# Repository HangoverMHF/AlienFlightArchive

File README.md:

## NOTE: This is an archival copy of the original CC BY-SA AlienFlight flight controllers. Preserved for posterity.

# AlienFlight

| [Classic FC](/Flight-Controllers/Classic#narrow-classic-flight-controller) | [F3 Quad FC](/Flight-Controllers/F3-V1/F3-Quad#f3-quad-brushed-v1-flight-controller) | [F3 Hexa FC](/Flight-Controllers/F3-V1/F3-Hexa#f3-hexa-brushed-v1-flight-controller) | [F3 Octo FC](/Flight-Controllers/F3-V1/F3-Octo#f3-octo-brushed-v1-flight-controller) |

## Objective

The goal of the AlienFlight project is to share some of my personal flight controller designs with fellow RC hobbyists, in hopes that this work might be useful. I want others to use, learn from, and enjoy this work in the same ways I have.

MAKE, SHARE, FLY!

### Contributing

Do you want to give back to this project? This project needs people who can help by providing:

* Board Specifications
* Documentation and Images
* How To tutorials

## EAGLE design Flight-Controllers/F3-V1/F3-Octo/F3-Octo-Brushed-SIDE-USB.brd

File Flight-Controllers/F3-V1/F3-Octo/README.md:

## NOTE: This is an archival copy of the original CC BY-SA AlienFlight flight controllers. Preserved for posterity.

## F3 Octo Brushed V1 Flight Controller

The F3 Brushed Octo V1 is an experimental flight controller designed to pilot Quadcopters, Hexacopters, and even Octocopters using 7mm-8.5mm brushed motors. It features an ARM STM32 F3 processor,  built in USB for easy firmware flashing, and parameter editing,  MPU6050 Gyro/Accelerometer, 7A ESCs, and a built in Bind switch for easy binding.
### F3 Octo Brushed V1 Example Picture
(JMPR build pictured - Latest build uses tactile switches in place of jumpers)

#### F3 Octo Brushed V1 Specifications

* Cleanflight compatible
* STM32 F3 MCU
* MPU6050 accelerometer/gyro sensor unit
* 4x 7A dual channel brushed ESCs (Mosfets) - 2 oz copper layers recommended
* Direct programming connection via side USB
* (*) serial connection for external DSM2/DSMX sat receiver (e.g. Spektrum SAT, OrangeRx R100 or Lemon RX)
* Alternate PPM receiver connection (i.e. Deltang Rx31)
* Hardware bind button for easy binding
* Boot button for easy firmware flashing
* Motor connections oriented for self explanatory connection
* Dimensions: 29x33mm (use thin FR4 material for weight savings)
* Direct operation from an single cell lipo battery
* All components arranged on the top layer

**NOTES:** Battery Voltage monitoring on 1S powered machines is not very effective (and is disabled by default in Cleanflight F3 firmware).

**Lost Model Alarm:** A small Buzzer with a low current draw (=<20mA) can be used in place of the VMON LED.  You can tie activation of this Buzzer to a switch on your Transmitter via the Beeper option, on the Cleanflight modes page.

**Octo Configuration:** In order to use Octo. you must select the custom mixer option on the Cleanflight Configuration page. Physical motor outputs are self explanatory.

#### Build Files and Resources:

Schematic and board design ➜ [F3 Octo Brushed V1 Eagle CAD Files](/Flight-Controllers/F3-V1/F3-Octo "F3 Octo Brushed V1 Eagle CAD Files") 

This bare board can be made at ➜ [OSH Park](https://oshpark.com/ "OSH Park")

Stencils can be made at ➜ [OSH Stencils](https://www.oshstencils.com/ "OSH Stencils")

_**THESE FILES ARE BEING PROVIDED ''AS IS'' WITHOUT ANY EXPRESS OR IMPLIED WARRANTIES.**_

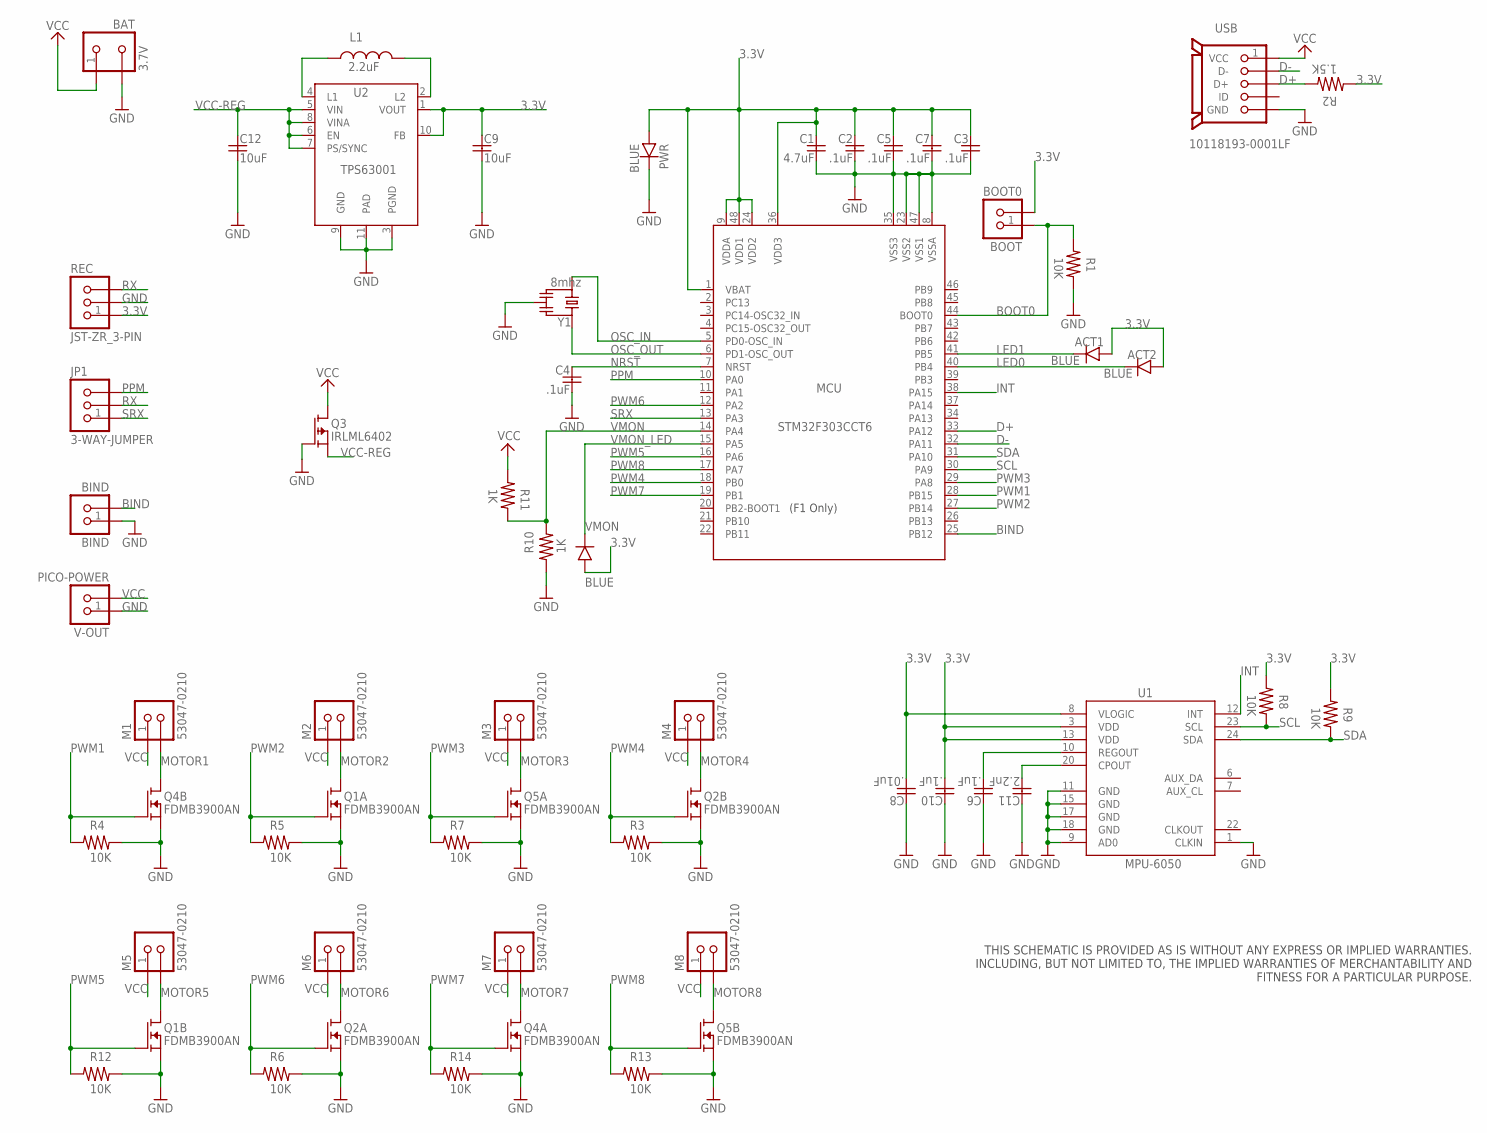
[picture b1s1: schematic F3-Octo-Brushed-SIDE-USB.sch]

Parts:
ACT1, ACT2: BLUE; SMD-CHIP-LED-0805
BAT: 3.7V; S2B-PH-K-S
BIND: BIND; B3U-1000P(M)
BOOT: BOOT0; B3U-1000P(M)
C1: 4.7uF; MUR-CAP-0603
C2, C3, C4, C5, C6, C7, C10: .1uF; MUR-CAP-0603
C8: .01uF; MUR-CAP-0603
C9, C12: 10uF; YUDEN-CAP-0805
C11: 2.2nF; MUR-CAP-0603
JP1: 3-WAY-JUMPER
L1: 2.2uF; NR301X
M1, M2, M3, M4, M5, M6, M7, M8: 53047-0210; PICO-53047-02
MCU: STM32F303CCT6; LQFP48-7X7
PWR: BLUE; SMD-CHIP-LED-0805
Q1, Q2, Q4, Q5: FDMB3900AN; 8-WDFN-DUAL
Q3: IRLML6402; SOT-23
R1, R3, R4, R5, R6, R7, R8, R9, R12, R13, R14: 10K; VISH-RES-0603
R2: 1.5K; VISH-RES-0603
R10, R11: 1K; VISH-RES-0603
REC: JST-ZR_3-PIN; S3B-ZR
U1: MPU-6050; QFN24-4X4
U2: TPS63001; VSON-N10
USB: 10118193-0001LF
V-OUT: PICO-POWER; PICO_1.25_.5MM
VMON: BLUE; SMD-CHIP-LED-0805
Y1: 8mhz; RESONATOR_8

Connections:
3.3V: ACT1.A, ACT2.A, BOOT.2, C1.1, C2.1, C3.1, C5.1, C7.1, C8.2, C9.1, C10.2, MCU.1 (VBAT), MCU.9 (VDDA), MCU.24 (VDD2), MCU.36 (VDD3), MCU.48 (VDD1), PWR.A, R2.2, R8.2, R9.2, REC.1, U1.3 (VDD), U1.8 (VLOGIC), U1.13 (VDD), U2.1 (VOUT), U2.10 (FB), VMON.A
BIND: BIND.2, MCU.25 (PB12)
BOOT0: BOOT.1, MCU.44 (BOOT0), R1.2
D+: MCU.33 (PA12), R2.1, USB.3 (D+)
D-: MCU.32 (PA11), USB.2 (D-)
GND: BAT.2, BIND.1, C1.2, C2.2, C3.2, C4.2, C5.2, C6.1, C7.2, C8.1, C9.2, C10.1, C11.1, C12.2, MCU.8 (VSSA), MCU.23 (VSS2), MCU.35 (VSS3), MCU.47 (VSS1), PWR.C, Q1.1@S1 (S), Q1.3@S1 (S), Q2.1@S1 (S), Q2.3@S1 (S), Q3.1 (G), Q4.1@S1 (S), Q4.3@S1 (S), Q5.1@S1 (S), Q5.3@S1 (S), R1.1, R3.1, R4.1, R5.1, R6.1, R7.1, R10.2, R12.1, R13.1, R14.1, REC.2, U1.1 (CLKIN), U1.9 (AD0), U1.11 (GND), U1.15 (GND), U1.17 (GND), U1.18 (GND), U2.3 (PGND), U2.9 (GND), U2.11 (PAD), USB.5 (GND), USB.GND, USB.GND2 (GND), USB.HOLE1 (GND), USB.HOLE2 (GND), V-OUT.1, Y1.2
INT: MCU.38 (PA15), U1.12 (INT)
LED0: ACT2.C, MCU.40 (PB4)
LED1: ACT1.C, MCU.41 (PB5)
MOTOR1: M1.2, Q4.5+6 (D)
MOTOR2: M2.2, Q1.7+8 (D)
MOTOR3: M3.2, Q5.7+8 (D)
MOTOR4: M4.2, Q2.5+6 (D)
MOTOR5: M5.2, Q1.5+6 (D)
MOTOR6: M6.2, Q2.7+8 (D)
MOTOR7: M7.2, Q4.7+8 (D)
MOTOR8: M8.2, Q5.5+6 (D)
unnamed: C6.2, U1.10 (REGOUT)
unnamed: C11.2, U1.20 (CPOUT)
unnamed: L1.2, U2.2 (L2)
unnamed: L1.1, U2.4 (L1)
NRST: C4.1, MCU.7 (NRST)
OSC_IN: MCU.5 (PD0-OSC_IN), Y1.3
OSC_OUT: MCU.6 (PD1-OSC_OUT), Y1.1
PPM: JP1.3, MCU.10 (PA0)
PWM1: MCU.28 (PB15), Q4.4@G2 (G), R4.2
PWM2: MCU.27 (PB14), Q1.2@G1 (G), R5.2
PWM3: MCU.29 (PA8), Q5.2@G1 (G), R7.2
PWM4: MCU.18 (PB0), Q2.4@G2 (G), R3.2
PWM5: MCU.16 (PA6), Q1.4@G2 (G), R12.2
PWM6: MCU.12 (PA2), Q2.2@G1 (G), R6.2
PWM7: MCU.19 (PB1), Q4.2@G1 (G), R14.2
PWM8: MCU.17 (PA7), Q5.4@G2 (G), R13.2
RX: JP1.2, REC.3
SCL: MCU.30 (PA9), R8.1, U1.23 (SCL)
SDA: MCU.31 (PA10), R9.1, U1.24 (SDA)
SRX: JP1.1, MCU.13 (PA3)
VCC: BAT.1, M1.1, M2.1, M3.1, M4.1, M5.1, M6.1, M7.1, M8.1, Q3.3 (D), R11.2, USB.1 (VCC), V-OUT.2
VCC-REG: C12.1, Q3.2 (S), U2.5 (VIN), U2.6 (EN), U2.7 (PS/SYNC), U2.8 (VINA)
VMON: MCU.14 (PA4), R10.1, R11.1
VMON_LED: MCU.15 (PA5), VMON.C

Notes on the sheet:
THIS SCHEMATIC IS PROVIDED AS IS WITHOUT ANY EXPRESS OR IMPLIED WARRANTIES. INCLUDING, BUT NOT LIMITED TO, THE IMPLIED WARRANTIES OF MERCHANTABILITY AND FITNESS FOR A PARTICULAR PURPOSE.

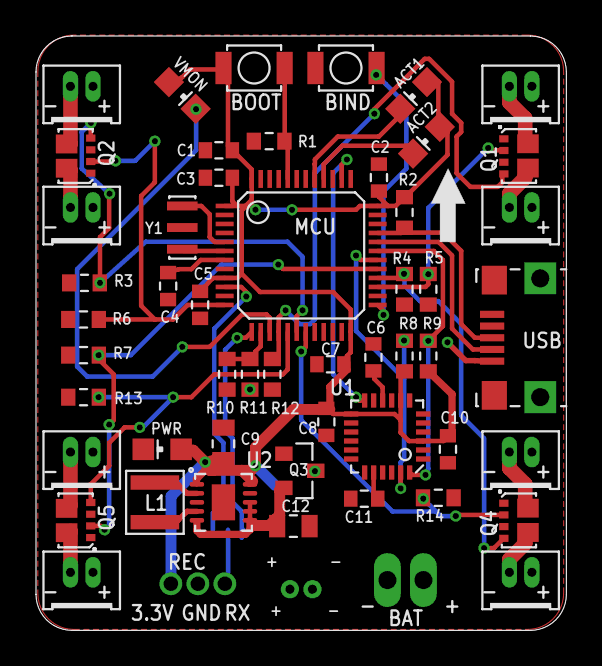
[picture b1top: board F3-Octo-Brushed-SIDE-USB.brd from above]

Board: 2 copper layers, 29.5 x 33.0 mm, 56 parts (1 on the bottom side), 41 nets.

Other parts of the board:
U$2: ARROW

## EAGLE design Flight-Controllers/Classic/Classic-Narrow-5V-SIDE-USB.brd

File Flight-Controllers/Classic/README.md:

## NOTE: This is an archival copy of the original CC BY-SA AlienFlight flight controllers. Preserved for posterity.

## Narrow Classic Flight Controller
The Classic Narrow is an experimental flight controller designed to pilot Quadcopters using 7mm-8.5mm brushed motors. It features an Atmel Atmega 32u4 processor, MPU6050 Gyro/Accelerometer,  built in 9.5A ESCs, and a built in Bind button for easy binding.
### Narrow Classic Example Picture

#### Narrow Classic Specs
* MultiWii compatible
* Atmel Atmega 32u4 micro controller
* MPU6050 accelerometer/gyro sensor unit
* 4x 9.5A brushed ESCs (MOSFETS) - 2oz copper layers recommended
* Integrated USB port (side access)
* Serial connection for external DSM2/DSMX sat receiver (e.g. Spektrum SAT, OrangeRx R100 or Lemon RX)
* Alternate PPM connection for external receiver - Pin pulled out - untested
* Hardware bind button for easy binding
* Motor connections are at the corners for easy orientation with reduced wiring
* Dimensions:  31x25mm
* Direct operation from an single cell 3.7V Lipo battery
* 5V and 3.3V buck/boost regulators (5V out can be used to power accessories)
* Buzzer out on pin D8
* Single Sided - all components on the top layer

#### Build Files and Resources:

Schematic and board design ➜ [Narrow Classic 5V Eagle CAD Files](/Flight-Controllers/Classic "Classic Narrow Eagle CAD Files") 

This bare board can be made at ➜ [OSH Park](https://oshpark.com/ "OSH Park")

Stencils can be made at ➜ [OSH Stencils](https://www.oshstencils.com/ "OSH Stencils")

_**THESE FILES ARE BEING PROVIDED ''AS IS'' WITHOUT ANY EXPRESS OR IMPLIED WARRANTIES.**_

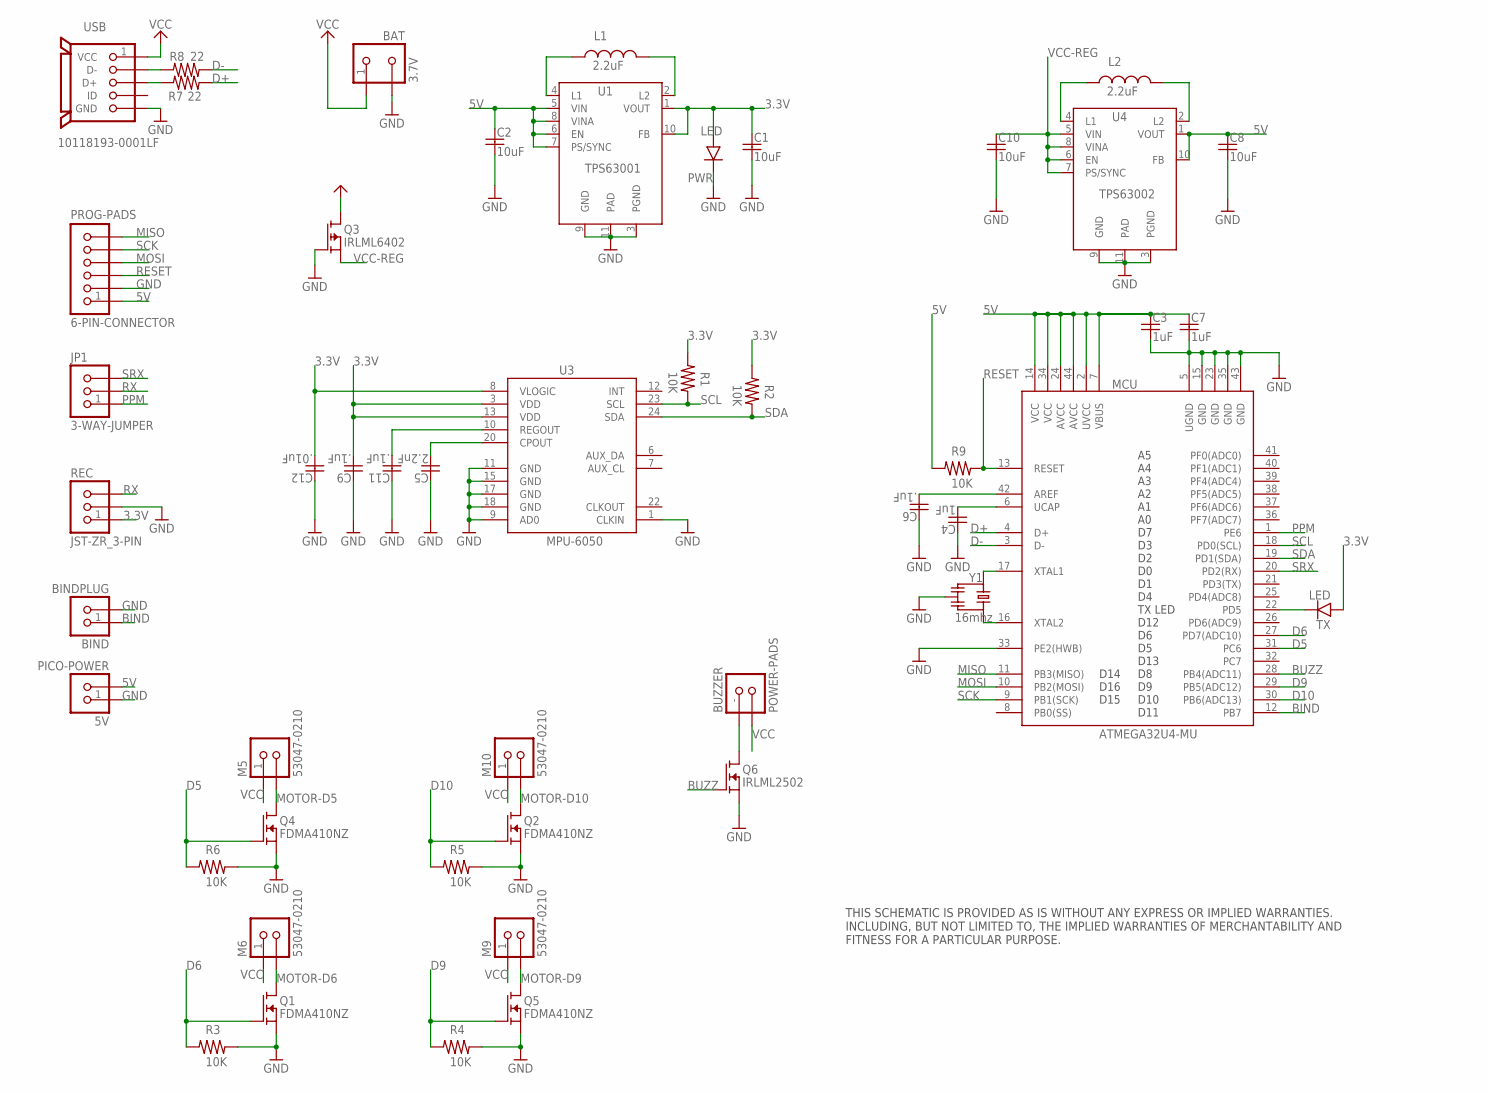
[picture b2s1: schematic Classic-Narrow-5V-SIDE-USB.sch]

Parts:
5V: PICO-POWER; PICO_1.25_.5MM
BAT: 3.7V; S2B-PH-K-S
BIND: BINDPLUG; B3U-1000P(M)
BUZZER: POWER-PADS; POW-PADS
C1, C2, C8, C10: 10uF; YUDEN-CAP-0805
C3, C4, C7: 1uF; MUR-CAP-0603
C5: 2.2nF; MUR-CAP-0603
C6, C9, C11: .1uF; MUR-CAP-0603
C12: .01uF; MUR-CAP-0603
JP1: 3-WAY-JUMPER
L1, L2: 2.2uF; NR301X
M5, M6, M9, M10: 53047-0210; PICO-53047-02
MCU: ATMEGA32U4-MU; QFN44-7X7
PROG-PADS: 6-PIN-CONNECTOR; B6B-ZR
PWR: LED; SMD-CHIP-LED-0805
Q1, Q2, Q4, Q5: FDMA410NZ; MICROFET-2X2
Q3: IRLML6402; SOT-23
Q6: IRLML2502; SOT-23
R1, R2, R3, R4, R5, R6, R9: 10K; VISH-RES-0603
R7, R8: 22; VISH-RES-0603
REC: JST-ZR_3-PIN; S3B-ZR
TX: LED; SMD-CHIP-LED-0805
U1: TPS63001; VSON-N10
U3: MPU-6050; QFN24-4X4
U4: TPS63002; VSON-N10
USB: 10118193-0001LF
Y1: 16mhz; RESONATOR_16

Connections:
3.3V: C1.1, C9.2, C12.2, PWR.A, R1.2, R2.2, REC.1, TX.A, U1.1 (VOUT), U1.10 (FB), U3.3 (VDD), U3.8 (VLOGIC), U3.13 (VDD)
5V: 5V.2, C2.1, C3.1, C7.1, C8.1, MCU.2 (UVCC), MCU.7 (VBUS), MCU.14 (VCC), MCU.24 (AVCC), MCU.34 (VCC), MCU.44 (AVCC), PROG-PADS.1, R9.2, U1.5 (VIN), U1.6 (EN), U1.7 (PS/SYNC), U1.8 (VINA), U4.1 (VOUT), U4.10 (FB)
AREF: C6.2, MCU.42 (AREF)
BIND: BIND.1, MCU.12 (PB7)
BUZZ: MCU.28 (PB4(ADC11)), Q6.1 (G)
D5: MCU.31 (PC6), Q4.G, R6.2
D6: MCU.27 (PD7(ADC10)), Q1.G, R3.2
D9: MCU.29 (PB5(ADC12)), Q5.G, R4.2
D10: MCU.30 (PB6(ADC13)), Q2.G, R5.2
D+: MCU.4 (D+), R7.1
D-: MCU.3 (D-), R8.1
GND: 5V.1, BAT.2, BIND.2, C1.2, C2.2, C3.2, C4.1, C5.1, C6.1, C7.2, C8.2, C9.1, C10.2, C11.1, C12.1, MCU.5 (UGND), MCU.15 (GND), MCU.23 (GND), MCU.33 (PE2(HWB)), MCU.35 (GND), MCU.43 (GND), PROG-PADS.2, PWR.C, Q1.S, Q1.S1 (S), Q2.S, Q2.S1 (S), Q3.1 (G), Q4.S, Q4.S1 (S), Q5.S, Q5.S1 (S), Q6.2 (S), R3.1, R4.1, R5.1, R6.1, REC.2, U1.3 (PGND), U1.9 (GND), U1.11 (PAD), U3.1 (CLKIN), U3.9 (AD0), U3.11 (GND), U3.15 (GND), U3.17 (GND), U3.18 (GND), U4.3 (PGND), U4.9 (GND), U4.11 (PAD), USB.5 (GND), USB.GND, USB.GND2 (GND), USB.HOLE1 (GND), USB.HOLE2 (GND), Y1.2
MISO: MCU.11 (PB3(MISO)), PROG-PADS.6
MOSI: MCU.10 (PB2(MOSI)), PROG-PADS.4
MOTOR-D5: M5.2, Q4.D, Q4.D1 (D), Q4.D2 (D), Q4.D3 (D), Q4.D4 (D)
MOTOR-D6: M6.2, Q1.D, Q1.D1 (D), Q1.D2 (D), Q1.D3 (D), Q1.D4 (D)
MOTOR-D9: M9.2, Q5.D, Q5.D1 (D), Q5.D2 (D), Q5.D3 (D), Q5.D4 (D)
MOTOR-D10: M10.2, Q2.D, Q2.D1 (D), Q2.D2 (D), Q2.D3 (D), Q2.D4 (D)
unnamed: MCU.17 (XTAL1), Y1.1
unnamed: MCU.16 (XTAL2), Y1.3
unnamed: R7.2, USB.3 (D+)
unnamed: C4.2, MCU.6 (UCAP)
unnamed: C11.2, U3.10 (REGOUT)
unnamed: R8.2, USB.2 (D-)
unnamed: MCU.22 (PD5), TX.C
unnamed: C5.2, U3.20 (CPOUT)
unnamed: L1.2, U1.2 (L2)
unnamed: BUZZER.- (1), Q6.3 (D)
unnamed: L1.1, U1.4 (L1)
unnamed: L2.2, U4.2 (L2)
unnamed: L2.1, U4.4 (L1)
PPM: JP1.1, MCU.1 (PE6)
RESET: MCU.13 (RESET), PROG-PADS.3, R9.1
RX: JP1.2, REC.3
SCK: MCU.9 (PB1(SCK)), PROG-PADS.5
SCL: MCU.18 (PD0(SCL)), R1.1, U3.23 (SCL)
SDA: MCU.19 (PD1(SDA)), R2.1, U3.24 (SDA)
SRX: JP1.3, MCU.20 (PD2(RX))
VCC: BAT.1, BUZZER.+ (2), M5.1, M6.1, M9.1, M10.1, Q3.3 (D), USB.1 (VCC)
VCC-REG: C10.1, Q3.2 (S), U4.5 (VIN), U4.6 (EN), U4.7 (PS/SYNC), U4.8 (VINA)

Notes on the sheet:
THIS SCHEMATIC IS PROVIDED AS IS WITHOUT ANY EXPRESS OR IMPLIED WARRANTIES. INCLUDING, BUT NOT LIMITED TO, THE IMPLIED WARRANTIES OF MERCHANTABILITY AND FITNESS FOR A PARTICULAR PURPOSE.

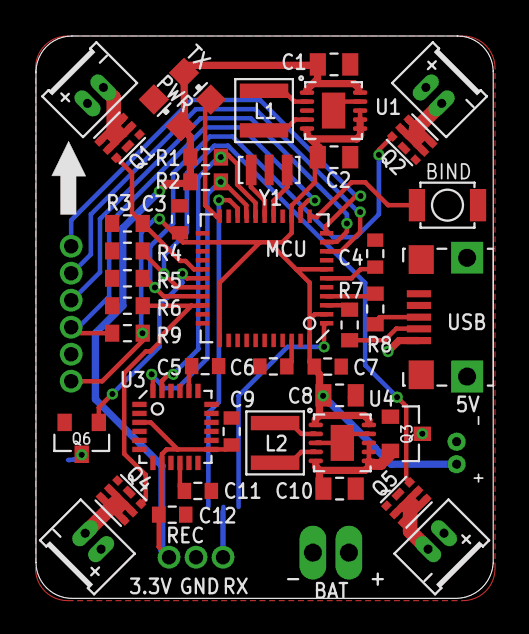
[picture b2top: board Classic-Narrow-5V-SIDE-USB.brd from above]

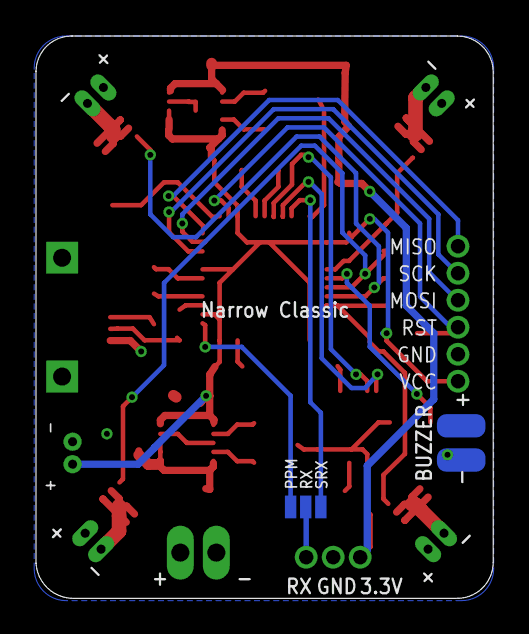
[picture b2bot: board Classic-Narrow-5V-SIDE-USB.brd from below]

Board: 2 copper layers, 25.4 x 31.2 mm, 49 parts (2 on the bottom side), 40 nets.

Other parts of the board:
U$1: ARROW

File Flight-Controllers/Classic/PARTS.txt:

Partlist exported from Classic-Narrow-5V-SIDE-USB-JMPR.sch

Part      Value            Description            MF          MPN                                    
5V        PICO-POWER       Pico Power Connector   Molex       53047-0210                             
BAT       3.7V             Battery Connector      JST         S2B-PH-K-S                             
BIND      BINDPLUG         Jumper                 Sullins     GRPB021VWVN-RC (JUMPER IS M50-1930005) 
BUZZER    POWER-PADS       Power Pads                                                                
C1        10uF             CAPACITORS             Taiyo Yuden JMK212AB7106KG-T                       
C2        10uF             CAPACITORS             Taiyo Yuden JMK212AB7106KG-T                       
C3        1uF              CAPACITORS             Murata      GRM188R71C105KA12D                     
C4        1uF              CAPACITORS             Murata      GRM188R71C105KA12D                     
C5        2.2nF            CAPACITORS             Murata      GRM188R71C222KA01D                     
C6        .1uF             CAPACITORS             Murata      GRM188R71C104KA01D                     
C7        1uF              CAPACITORS             Murata      GRM188R71C105KA12D                     
C8        10uF             CAPACITORS             Taiyo Yuden JMK212AB7106KG-T                       
C9        .1uF             CAPACITORS             Murata      GRM188R71C104KA01D                     
C10       10uF             CAPACITORS             Taiyo Yuden JMK212AB7106KG-T                       
C11       .1uF             CAPACITORS             Murata      GRM188R71C104KA01D                     
C12       .01uF            CAPACITORS             Murata      GRM188R71C103KA01D                     
JP1       3-WAY-JUMPER     3 Way Jumper                                                              
L1        2.2uF            3X3mm Inductor         Taiyo Yuden NR3015T2R2M                            
L2        2.2uF            3X3mm Inductor         Taiyo Yuden NR3015T2R2M                            
M5        53047-0210       Motor Connector        MOLEX       53047-0210                             
M6        53047-0210       Motor Connector        MOLEX       53047-0210                             
M9        53047-0210       Motor Connector        MOLEX       53047-0210                             
M10       53047-0210       Motor Connector        MOLEX       53047-0210                             
MCU       ATMEGA32U4-MU    Atmega32U4-MU          Atmel       Atmega32U4-MU                          
PROG-PADS 6-PIN-CONNECTOR  6-PIN CONNECTOR        JST         B6B-ZR(LF)(SN)                         
PWR       LED              SMD CHIP LED           Kingbright  APHCM2012QBC/D-F01                     
Q1        FDMA410NZ        N-Channel MOSFET       Fairchild   FDMA410NZ                              
Q2        FDMA410NZ        N-Channel MOSFET       Fairchild   FDMA410NZ                              
Q3        IRLML6402        P-Channel MOSFET       IR          IRLML6402                              
Q4        FDMA410NZ        N-Channel MOSFET       Fairchild   FDMA410NZ                              
Q5        FDMA410NZ        N-Channel MOSFET       Fairchild   FDMA410NZ                              
Q6        IRLML2502        N-Channel MOSFET       IR          IRLML2502                              
R1        10K              RESISTORS              Vishay      CRCW060310K0FKEAHP                     
R2        10K              RESISTORS              Vishay      CRCW060310K0FKEAHP                     
R3        10K              RESISTORS              Vishay      CRCW060310K0FKEAHP                     
R4        10K              RESISTORS              Vishay      CRCW060310K0FKEAHP                     
R5        10K              RESISTORS              Vishay      CRCW060310K0FKEAHP                     
R6        10K              RESISTORS              Vishay      CRCW060310K0FKEAHP                     
R7        22               RESISTORS              Vishay      CRCW060322R0FKEAHP                     
R8        22               RESISTORS              Vishay      CRCW060322R0FKEAHP                     
R9        10K              RESISTORS              Vishay      CRCW060310K0FKEAHP                     
REC       JST-ZR_3-PIN     3 Pin Receiver         JST         S3B-ZR                                 
TX        LED              SMD CHIP LED           Kingbright  APHCM2012QBC/D-F01                     
U1        TPS63001         Buck/Boost Converter   TI          TPS63001DRCR                           
U3        MPU-6050         MPU-6050               Invensense  MPU-6050                               
U4        TPS63002         Buck/Boost Converter   TI          TPS63002DRCR                           
USB       10118193-0001LF  Micro-B USB Connector  FCI         10118193-0001LF                        
Y1        16mhz            SMD Ceramic Resonators Murata      CSTCE16M0V53-R0

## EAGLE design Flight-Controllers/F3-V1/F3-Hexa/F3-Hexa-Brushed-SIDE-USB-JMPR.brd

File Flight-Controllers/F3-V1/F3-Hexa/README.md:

## NOTE: This is an archival copy of the original CC BY-SA AlienFlight flight controllers. Preserved for posterity.

## F3 Hexa Brushed V1 Flight Controller

The F3 Brushed Hexa is an experimental flight controller designed to pilot Quadcopters or Hexacopters using 7mm-8.5mm brushed motors. It features an ARM STM32 F3 processor, built in side USB for easy firmware flashing, and parameter editing, MPU6050 Gyro/Accelerometer, dual channel 5A ESCs, and a built in Bind switch for hassle free binding.

### F3 Hexa Brushed V1 Example Picture
(JMPR build pictured - Latest build uses tactile switches in place of jumpers)

#### F3 Hexa Brushed V1 Specifications

* Cleanflight/Betaflight compatible
* STM32 F3 MCU
* MPU6050 accelerometer/gyro sensor unit
* 4X dual channel 5A brushed ESCs (Mosfets)- 2oz copper layers recommended
* Direct programming connection via side USB
* (*) serial connection for external DSM2/DSMX sat receiver (e.g. Spektrum SAT, OrangeRx R100 or Lemon RX)
* Alternate PPM receiver connection (i.e. Deltang Rx31)
* Hardware bind button for easy binding
* Boot bind button for easy firmware flashing
* Motor connections oriented for self explanatory connection
* Dimensions: 27x31mm (use thin FR4 material for weight savings)
* Direct operation from an single cell lipo battery

#### Build Files and Resources:

Schematic and board design ➜ [F3 Hexa Brushed V1 Eagle CAD Files](/Flight-Controllers/F3-V1/F3-Hexa "F3 Hexa Brushed V1 Eagle CAD Files") 

This bare board can be made at ➜ [OSH Park](https://oshpark.com/ "OSH Park")

Stencils can be made at ➜ [OSH Stencils](https://www.oshstencils.com/ "OSH Stencils")

_**THESE FILES ARE BEING PROVIDED ''AS IS'' WITHOUT ANY EXPRESS OR IMPLIED WARRANTIES.**_

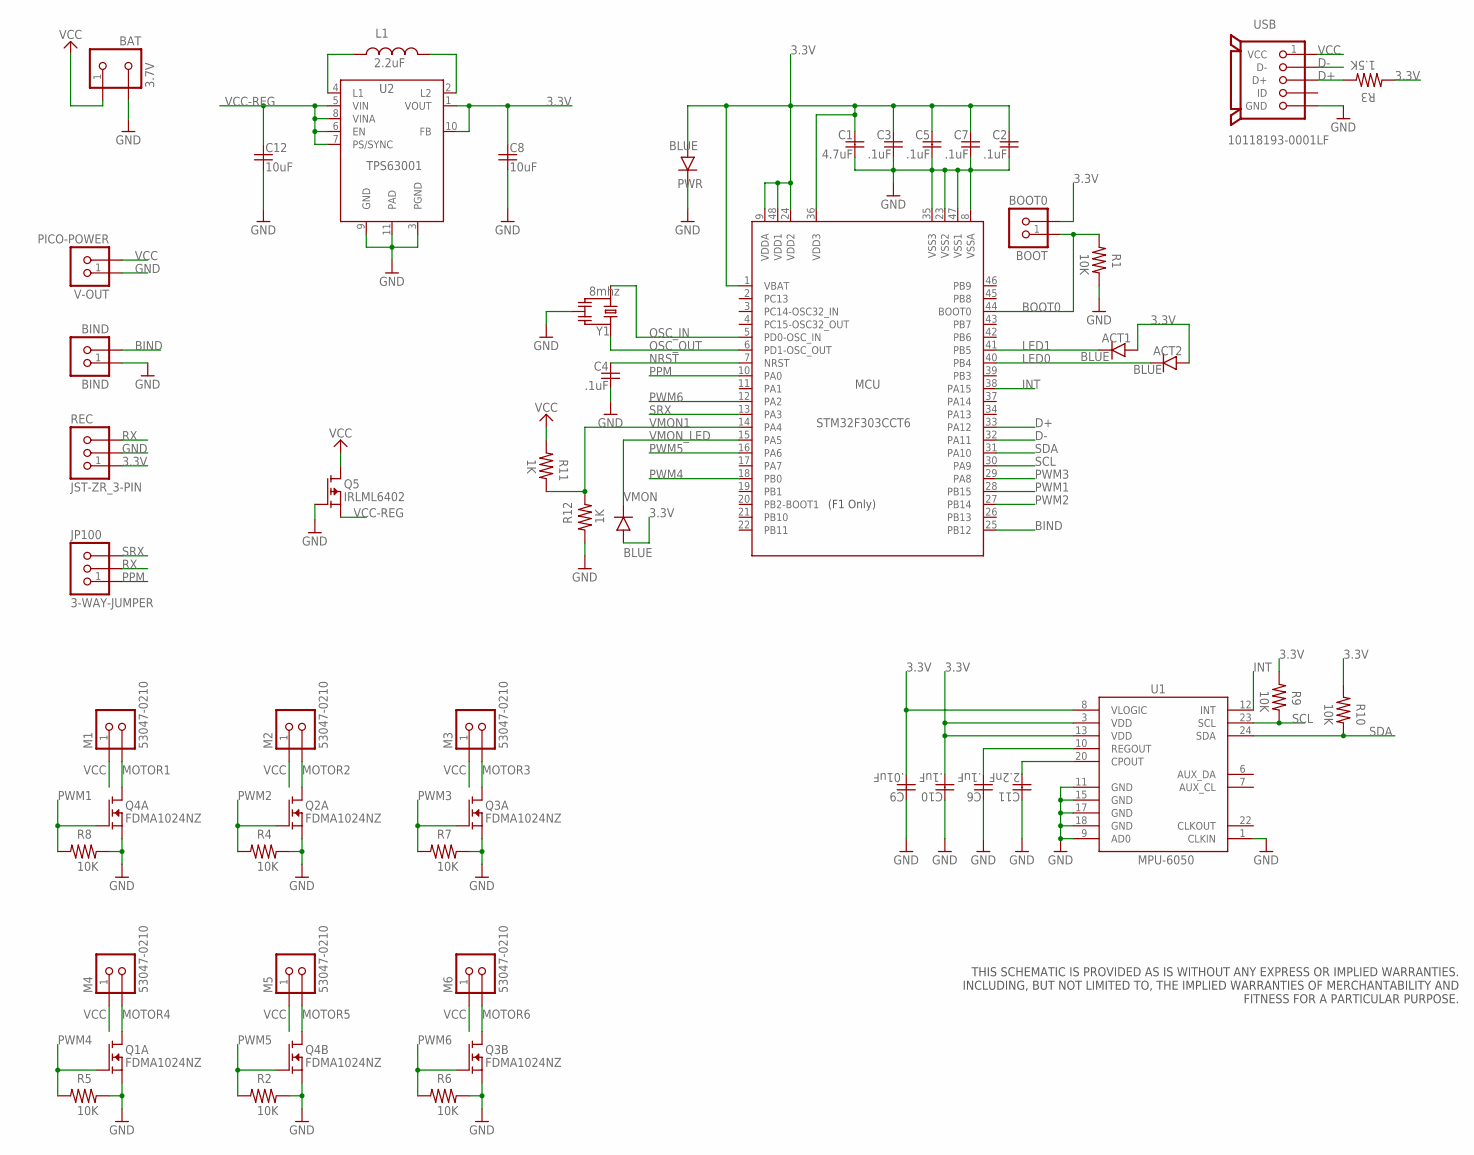
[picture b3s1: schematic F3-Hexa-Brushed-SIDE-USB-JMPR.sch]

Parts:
ACT1, ACT2: BLUE; SMD-CHIP-LED-0805
BAT: 3.7V; S2B-PH-K-S
BIND: BIND; 1.27MM-PINHEADX2
BOOT: BOOT0; 1.27MM-PINHEADX2
C1: 4.7uF; MUR-CAP-0603
C2, C3, C4, C5, C6, C7, C10: .1uF; MUR-CAP-0603
C8, C12: 10uF; YUDEN-CAP-0805
C9: .01uF; MUR-CAP-0603
C11: 2.2nF; MUR-CAP-0603
JP100: 3-WAY-JUMPER
L1: 2.2uF; NR301X
M1, M2, M3, M4, M5, M6: 53047-0210; PICO-53047-02
MCU: STM32F303CCT6; LQFP48-7X7
PWR: BLUE; SMD-CHIP-LED-0805
Q1, Q2, Q3, Q4: FDMA1024NZ; MICROFET-2X2_DUAL
Q5: IRLML6402; SOT-23
R1, R2, R4, R5, R6, R7, R8, R9, R10: 10K; VISH-RES-0603
R3: 1.5K; VISH-RES-0603
R11, R12: 1K; VISH-RES-0603
REC: JST-ZR_3-PIN; S3B-ZR
U1: MPU-6050; QFN24-4X4
U2: TPS63001; VSON-N10
USB: 10118193-0001LF
V-OUT: PICO-POWER; PICO_1.25_.5MM
VMON: BLUE; SMD-CHIP-LED-0805
Y1: 8mhz; RESONATOR_8

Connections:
3.3V: ACT1.A, ACT2.A, BOOT.2, C1.1, C2.1, C3.1, C5.1, C7.1, C8.1, C9.2, C10.2, MCU.1 (VBAT), MCU.9 (VDDA), MCU.24 (VDD2), MCU.36 (VDD3), MCU.48 (VDD1), PWR.A, R3.2, R9.2, R10.2, REC.1, U1.3 (VDD), U1.8 (VLOGIC), U1.13 (VDD), U2.1 (VOUT), U2.10 (FB), VMON.A
BIND: BIND.2, MCU.25 (PB12)
BOOT0: BOOT.1, MCU.44 (BOOT0), R1.2
D+: MCU.33 (PA12), R3.1, USB.3 (D+)
D-: MCU.32 (PA11), USB.2 (D-)
GND: BAT.2, BIND.1, C1.2, C2.2, C3.2, C4.2, C5.2, C6.1, C7.2, C8.2, C9.1, C10.1, C11.1, C12.2, MCU.8 (VSSA), MCU.23 (VSS2), MCU.35 (VSS3), MCU.47 (VSS1), PWR.C, Q1.A.S (S), Q2.A.S (S), Q3.A.S (S), Q3.B.S (S), Q4.A.S (S), Q4.B.S (S), Q5.1 (G), R1.1, R2.1, R4.1, R5.1, R6.1, R7.1, R8.1, R12.2, REC.2, U1.1 (CLKIN), U1.9 (AD0), U1.11 (GND), U1.15 (GND), U1.17 (GND), U1.18 (GND), U2.3 (PGND), U2.9 (GND), U2.11 (PAD), USB.5 (GND), USB.GND, USB.GND2 (GND), USB.HOLE1 (GND), USB.HOLE2 (GND), V-OUT.1, Y1.2
INT: MCU.38 (PA15), U1.12 (INT)
LED0: ACT2.C, MCU.40 (PB4)
LED1: ACT1.C, MCU.41 (PB5)
MOTOR1: M1.2, Q4.A.D (D), Q4.A.D1 (D)
MOTOR2: M2.2, Q2.A.D (D), Q2.A.D1 (D)
MOTOR3: M3.2, Q3.A.D (D), Q3.A.D1 (D)
MOTOR4: M4.2, Q1.A.D (D), Q1.A.D1 (D)
MOTOR5: M5.2, Q4.B.D (D), Q4.B.D1 (D)
MOTOR6: M6.2, Q3.B.D (D), Q3.B.D1 (D)
unnamed: C6.2, U1.10 (REGOUT)
unnamed: C11.2, U1.20 (CPOUT)
unnamed: L1.2, U2.2 (L2)
unnamed: L1.1, U2.4 (L1)
NRST: C4.1, MCU.7 (NRST)
OSC_IN: MCU.5 (PD0-OSC_IN), Y1.3
OSC_OUT: MCU.6 (PD1-OSC_OUT), Y1.1
PPM: JP100.1, MCU.10 (PA0)
PWM1: MCU.28 (PB15), Q4.A.G (G), R8.2
PWM2: MCU.27 (PB14), Q2.A.G (G), R4.2
PWM3: MCU.29 (PA8), Q3.A.G (G), R7.2
PWM4: MCU.18 (PB0), Q1.A.G (G), R5.2
PWM5: MCU.16 (PA6), Q4.B.G (G), R2.2
PWM6: MCU.12 (PA2), Q3.B.G (G), R6.2
RX: JP100.2, REC.3
SCL: MCU.30 (PA9), R9.1, U1.23 (SCL)
SDA: MCU.31 (PA10), R10.1, U1.24 (SDA)
SRX: JP100.3, MCU.13 (PA3)
VCC: BAT.1, M1.1, M2.1, M3.1, M4.1, M5.1, M6.1, Q5.3 (D), R11.2, USB.1 (VCC), V-OUT.2
VCC-REG: C12.1, Q5.2 (S), U2.5 (VIN), U2.6 (EN), U2.7 (PS/SYNC), U2.8 (VINA)
VMON1: MCU.14 (PA4), R11.1, R12.1
VMON_LED: MCU.15 (PA5), VMON.C

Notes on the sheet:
THIS SCHEMATIC IS PROVIDED AS IS WITHOUT ANY EXPRESS OR IMPLIED WARRANTIES. INCLUDING, BUT NOT LIMITED TO, THE IMPLIED WARRANTIES OF MERCHANTABILITY AND FITNESS FOR A PARTICULAR PURPOSE.

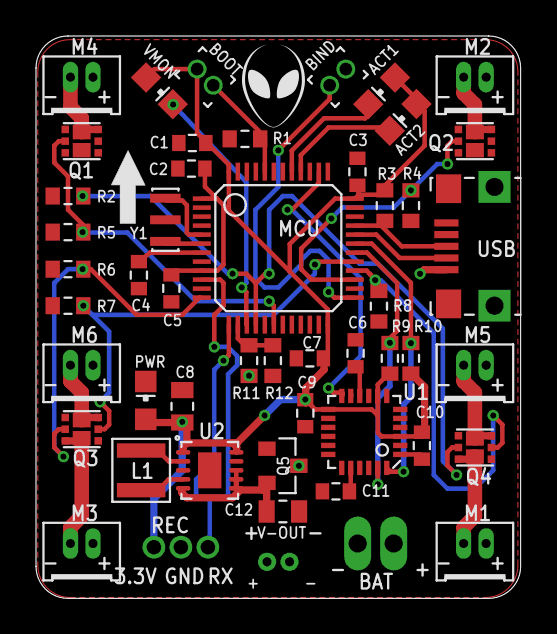
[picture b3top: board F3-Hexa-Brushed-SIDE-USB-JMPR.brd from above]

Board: 2 copper layers, 26.9 x 31.2 mm, 53 parts (1 on the bottom side), 37 nets.

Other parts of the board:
U$1: ARROW
U$2: ALIENHEADSMALL

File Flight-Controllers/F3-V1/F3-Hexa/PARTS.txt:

Partlist exported from F3-Hexa-Brushed-SIDE-USB-JMPR.sch

Part  Value            Description            MF          MPN                                    
ACT1  BLUE             SMD CHIP LED           Kingbright  APHCM2012QBC/D-F01                     
ACT2  BLUE             SMD CHIP LED           Kingbright  APHCM2012QBC/D-F01                     
BAT   3.7V             Battery Connector      JST         S2B-PH-K-S                             
BIND  BIND             Jumper                 Sullins     GRPB021VWVN-RC (JUMPER IS M50-1930005) 
BOOT  BOOT0            Jumper                 Sullins     GRPB021VWVN-RC (JUMPER IS M50-1930005) 
C1    4.7uF            CAPACITORS             Murata      GRJ188C70J475KE11D                     
C2    .1uF             CAPACITORS             Murata      GRM188R71C104KA01D                     
C3    .1uF             CAPACITORS             Murata      GRM188R71C104KA01D                     
C4    .1uF             CAPACITORS             Murata      GRM188R71C104KA01D                     
C5    .1uF             CAPACITORS             Murata      GRM188R71C104KA01D                     
C6    .1uF             CAPACITORS             Murata      GRM188R71C104KA01D                     
C7    .1uF             CAPACITORS             Murata      GRM188R71C104KA01D                     
C8    10uF             CAPACITORS             Taiyo Yuden JMK212AB7106KG-T                       
C9    .01uF            CAPACITORS             Murata      GRM188R71C103KA01D                     
C10   .1uF             CAPACITORS             Murata      GRM188R71C104KA01D                     
C11   2.2nF            CAPACITORS             Murata      GRM188R71C222KA01D                     
C12   10uF             CAPACITORS             Taiyo Yuden JMK212AB7106KG-T                       
JP100 3-WAY-JUMPER     3 Way Jumper                                                              
L1    2.2uF            3X3mm Inductor         Taiyo Yuden NR3015T2R2M                            
M1    53047-0210       Motor Connector        MOLEX       53047-0210                             
M2    53047-0210       Motor Connector        MOLEX       53047-0210                             
M3    53047-0210       Motor Connector        MOLEX       53047-0210                             
M4    53047-0210       Motor Connector        MOLEX       53047-0210                             
M5    53047-0210       Motor Connector        MOLEX       53047-0210                             
M6    53047-0210       Motor Connector        MOLEX       53047-0210                             
MCU   STM32F303CCT6    STM32F32FX03           ST          STM32F303CCT6                          
PWR   BLUE             SMD CHIP LED           Kingbright  APHCM2012QBC/D-F01                     
Q1    FDMA1024NZ       Dual N-Channel MOSFET  Fairchild   FDMA1024NZ                             
Q2    FDMA1024NZ       Dual N-Channel MOSFET  Fairchild   FDMA1024NZ                             
Q3    FDMA1024NZ       Dual N-Channel MOSFET  Fairchild   FDMA1024NZ                             
Q4    FDMA1024NZ       Dual N-Channel MOSFET  Fairchild   FDMA1024NZ                             
Q5    IRLML6402        P-Channel MOSFET       IR          IRLML6402                              
R1    10K              RESISTORS              Vishay      CRCW060310K0FKEAHP                     
R2    10K              RESISTORS              Vishay      CRCW060310K0FKEAHP                     
R3    1.5K             RESISTORS              Vishay      CRCW06031K50FKEAHP                     
R4    10K              RESISTORS              Vishay      CRCW060310K0FKEAHP                     
R5    10K              RESISTORS              Vishay      CRCW060310K0FKEAHP                     
R6    10K              RESISTORS              Vishay      CRCW060310K0FKEAHP                     
R7    10K              RESISTORS              Vishay      CRCW060310K0FKEAHP                     
R8    10K              RESISTORS              Vishay      CRCW060310K0FKEAHP                     
R9    10K              RESISTORS              Vishay      CRCW060310K0FKEAHP                     
R10   10K              RESISTORS              Vishay      CRCW060310K0FKEAHP                     
R11   1K               RESISTORS              Vishay      CRCW06031K00FKEAHP                     
R12   1K               RESISTORS              Vishay      CRCW06031K00FKEAHP                     
REC   JST-ZR_3-PIN     3 Pin Receiver         JST         S3B-ZR                                 
U1    MPU-6050         MPU-6050               Invensense  MPU-6050                               
U2    TPS63001         Buck/Boost Converter   TI          TPS63001DRCR                           
USB   10118193-0001LF  Micro-B USB Connector  FCI         10118193-0001LF                        
V-OUT PICO-POWER       Pico Power Connector   Molex       53047-0210                             
VMON  BLUE             SMD CHIP LED           Kingbright  APHCM2012QBC/D-F01                     
Y1    8mhz             SMD Ceramic Resonators Murata      CSTCE8M00G55-R0

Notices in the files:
Flight-Controllers/Classic/Classic-Narrow-5V-SIDE-USB.brd:
License:  CC BY SA
Released under the Creative Commons Attribution Share-Alike 4.0 License
http://creativecommons.org/licenses/by-sa/4.0
parts and their libraries:
alienflight: Released under the Creative Commons
Attribution Share-Alike 4.0 License
